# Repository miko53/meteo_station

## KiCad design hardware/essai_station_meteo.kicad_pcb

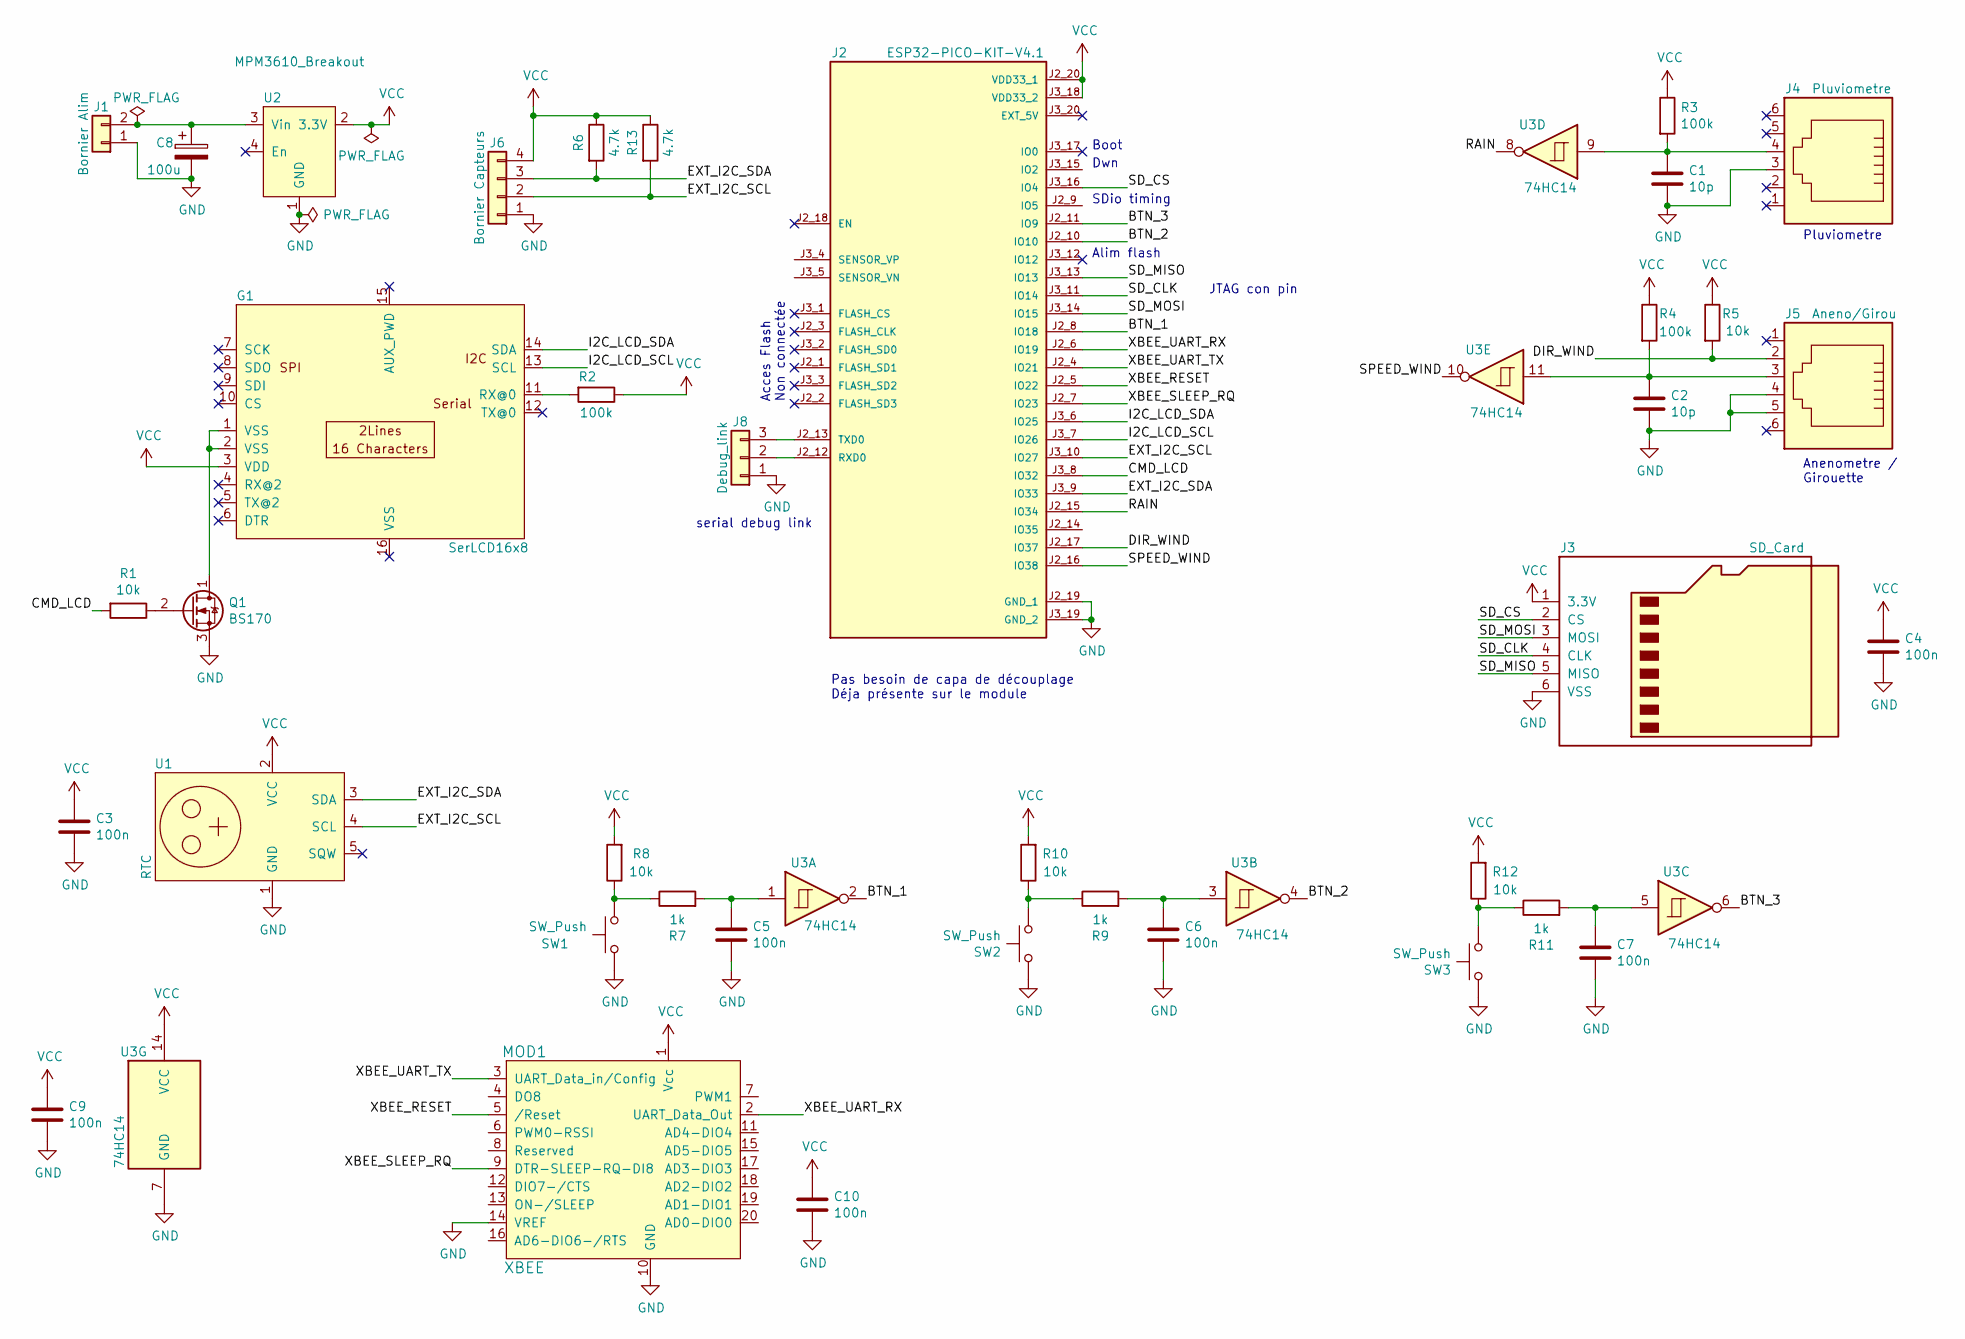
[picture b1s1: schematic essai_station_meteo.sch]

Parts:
C1, C2: 10p; C_Disc_D3.0mm_W1.6mm_P2.50mm
C3, C4, C5, C6, C7, C9, C10: 100n; C_Disc_D6.0mm_W2.5mm_P5.00mm
C8: 100u; CP_Radial_D8.0mm_P3.50mm
G1: SerLCD16x8; SerLCD16x8Sparkfun
J1: Bornier Alim; Bornier_2pts_L10mm_W7.5mm_P5mm
J2: ESP32-PICO-KIT-V4.1; XCVR_ESP32-PICO-KIT-V4.1; PARTREV 4.1
J3: SD_Card; PinHeader_1x06_P2.54mm_Vertical
J4: Pluviometre; RJ12_Amphenol_54601
J5: Aneno/Girou; RJ12_Amphenol_54601
J6: Bornier Capteurs; PinHeader_1x04_P2.54mm_Vertical
J8: Debug_link; PinHeader_1x03_P2.54mm_Vertical
MOD1: XBEE; XBEE-20_THT; MPN XB24-API-001; Digi-Key_PN 602-1273-ND
Q1: BS170; TO-92_Inline
R1, R5, R8, R10, R12: 10k; R_Axial_DIN0207_L6.3mm_D2.5mm_P10.16mm_Horizontal
R2, R3, R4: 100k; R_Axial_DIN0207_L6.3mm_D2.5mm_P10.16mm_Horizontal
R6, R13: 4.7k; R_Axial_DIN0207_L6.3mm_D2.5mm_P10.16mm_Horizontal
R7, R9, R11: 1k; R_Axial_DIN0207_L6.3mm_D2.5mm_P10.16mm_Horizontal
SW1, SW2, SW3: SW_Push; PinSocket_1x02_P2.54mm_Vertical
U1: RTC; PinHeader_1x05_P2.54mm_Vertical
U2: MPM3610_Breakout; PinSocket_1x04_P2.54mm_Vertical
U3: 74HC14; DIP-14_W7.62mm

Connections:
/BTN_1: J2.J2_8 (IO18), U3.2
/BTN_2: J2.J2_10 (IO10), U3.4
/BTN_3: J2.J2_11 (IO9), U3.6
/CMD_LCD: J2.J3_8 (IO32), R1.2
/DIR_WIND: J2.J2_17 (IO37), J5.2, R5.2
/EXT_I2C_SCL: J2.J3_10 (IO27), J6.2, R13.2, U1.4 (SCL)
/EXT_I2C_SDA: J2.J3_9 (IO33), J6.3, R6.2, U1.3 (SDA)
/I2C_LCD_SCL: G1.13 (SCL), J2.J3_7 (IO26)
/I2C_LCD_SDA: G1.14 (SDA), J2.J3_6 (IO25)
/RAIN: J2.J2_15 (IO34), U3.8
/SD_CLK: J2.J3_11 (IO14), J3.4 (CLK)
/SD_CS: J2.J3_16 (IO4), J3.2 (CS)
/SD_MISO: J2.J3_13 (IO13), J3.5 (MISO)
/SD_MOSI: J2.J3_14 (IO15), J3.3 (MOSI)
/SPEED_WIND: J2.J2_16 (IO38), U3.10
/XBEE_RESET: J2.J2_5 (IO22), MOD1.5 (/Reset); also elsewhere on the board
/XBEE_SLEEP_RQ: J2.J2_7 (IO23), MOD1.9 (DTR-SLEEP-RQ-DI8); also elsewhere on the board
/XBEE_UART_RX: J2.J2_6 (IO19), MOD1.2 (UART_Data_Out); also elsewhere on the board
/XBEE_UART_TX: J2.J2_4 (IO21), MOD1.3 (UART_Data_in/Config); also elsewhere on the board
GND: C1.2, C2.2, C3.2, C4.2, C5.2, C6.2, C7.2, C8.2, C9.2, C10.2, J1.1, J2.J2_19 (GND_1), J2.J3_19 (GND_2), J3.6 (VSS), J4.3, J5.4, J5.5, J6.1, J8.1, MOD1.10 (GND), MOD1.14 (VREF), Q1.3 (S), SW1.1, SW2.1, SW3.1, U1.1 (GND), U2.1 (GND), U3.7 (GND); also elsewhere on the board
unnamed: C1.1, J4.4, R3.2, U3.9
unnamed: C2.1, J5.3, R4.2, U3.11
unnamed: C5.1, R7.2, U3.1
unnamed: C6.1, R9.2, U3.3
unnamed: C7.1, R11.2, U3.5
unnamed: C8.1, J1.2, U2.3 (Vin)
unnamed: G1.1 (VSS), G1.2 (VSS), Q1.1 (D)
unnamed: G1.11 (RX@0), R2.2
unnamed: J2.J2_12 (RXD0), J8.2
unnamed: J2.J2_13 (TXD0), J8.3
unnamed: Q1.2 (G), R1.1
unnamed: R7.1, R8.1, SW1.2
unnamed: R9.1, R10.1, SW2.2
unnamed: R11.1, R12.1, SW3.2
VCC: C3.1, C4.1, C9.1, C10.1, G1.3 (VDD), J2.J2_20 (VDD33_1), J2.J3_18 (VDD33_2), J3.1 (3.3V), J6.4, MOD1.1 (Vcc), R2.1, R3.1, R4.1, R5.1, R6.1, R8.2, R10.2, R12.2, R13.1, U1.2 (VCC), U2.2 (3.3V), U3.14 (VCC); also elsewhere on the board

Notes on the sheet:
Pas besoin de capa de découplage Déja présente sur le module
Pluviometre
Anenometre / Girouette
serial debug link
Boot
Alim flash
Acces Flash Non connectée
Dwn
SDio timing
JTAG con pin

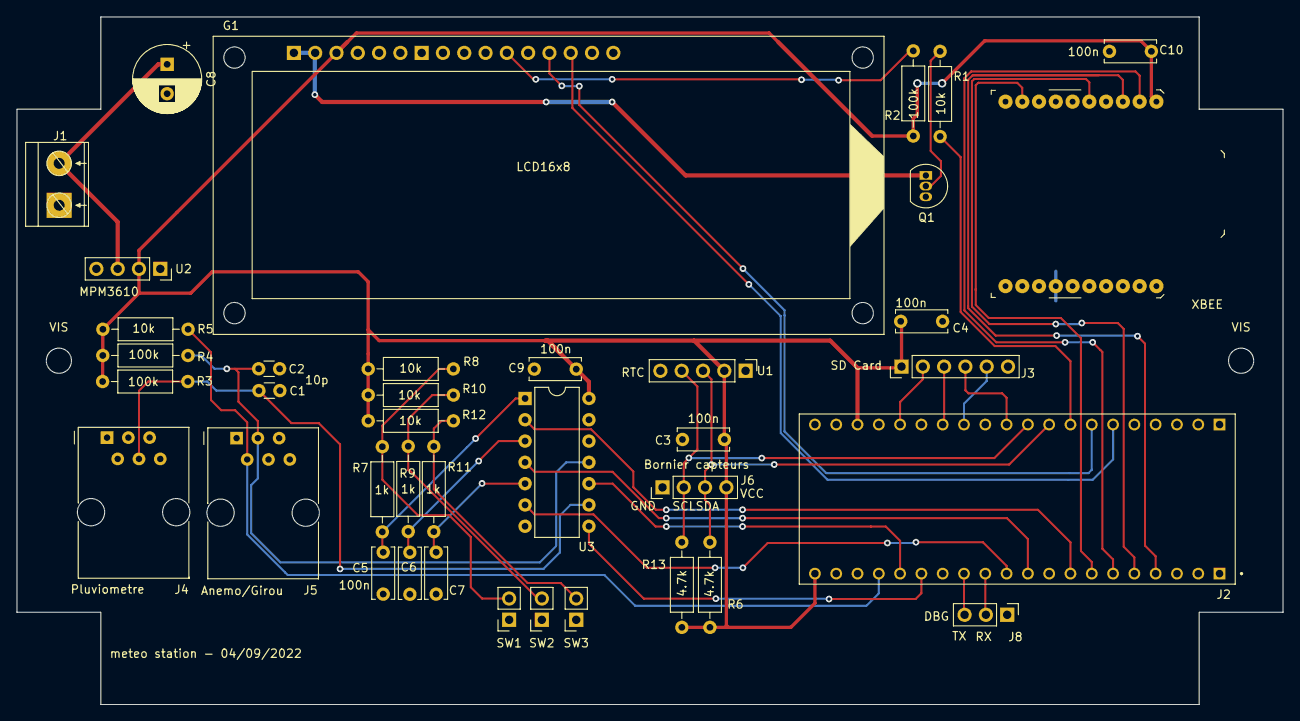
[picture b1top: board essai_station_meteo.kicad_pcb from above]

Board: 2 copper layers, 151.0 x 82.0 mm, 41 parts (0 on the bottom side), 35 nets.

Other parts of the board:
VIS: MountingHole_3mm
VIS#2: MountingHole_3mm
XBEE: XBEE; XBEE-20_THT

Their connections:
/XBEE_RESET: XBEE.5; also elsewhere on the board
/XBEE_SLEEP_RQ: XBEE.9; also elsewhere on the board
/XBEE_UART_RX: XBEE.2; also elsewhere on the board
/XBEE_UART_TX: XBEE.3; also elsewhere on the board
GND: XBEE.10, XBEE.14; also elsewhere on the board
VCC: XBEE.1; also elsewhere on the board

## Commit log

2022-09-04 schematics of meteo station
2022-09-04 add name of board + move capa to avoid RTC collision
2022-09-18 add initial readme
2022-09-24 add hello world for started...
2022-09-24 add I2C init + template of first files
2022-09-24 remove kdev file project
2022-09-25 first driver for ser_lcd screen, freely inspired from arduino one
2022-09-25 ser_lcd add new API
2022-09-25 add more API for ser_lcd, set tick to 1ms for wait time (may be review this)
2022-10-08 add first button events, work in progress
2022-10-09 add button driver
2022-10-09 add first menu, need more work (click to add in button for ex.) to save it
2022-10-10 add clicked() event
2022-10-15 clean up and reorganize menu, add setup date menu
2022-10-15 add time mgt
2022-10-15 add rtc driver for pcf8523 with date/time setting
2022-10-16 add date/time display dynamically
2022-10-16 add sdcard support
2022-10-16 add sdcard infos screen
2022-10-23 begin file log creation and fix some error on date, plus some improvement
2022-10-23 fix error when trying to send an empty line to ser_lcd
2022-10-23 create task in filelog clean up code
2022-10-29 add ctrl task + public API for filelog
2022-10-30 add modification of file when date has changed + test in ctrl task
2022-10-30 add first dev for rainmeter
2022-10-30 fix init status check
2022-10-30 add anemometer like rainmeter and modify conversion formula
2022-10-31 adapt formula according to documentation, need to be checked since the chinese version give 0.33m/s and not 0.66....
2022-10-31 add wind direction
2022-10-31 simplify including header files
2022-10-31 centralize thread info, add data_def for manage data reception in ctrl
2022-10-31 centralize configuration, remove some dbg information, add it in ctrl
2022-10-31 change log/dbg info
2022-10-31 add first log of data in sd card
2022-10-31 add API for date and write log data on SD card
2022-11-01 update gitignore for vscode
2022-11-01 first DB (trial) for doing calculation and data storage
2022-11-01 add unit test for all operation on data, first step (WIP)
2022-11-01 wip to save, first dev on data
2022-11-13 first test on cumul data
2022-11-13 add complementary test on slide part of data_operation
2022-11-20 add code for fix period and unit test for helper functions to prepare unit test
2022-11-20 add day which begins by 1
2022-11-20 add unit test
2022-11-20 add test case + bug fix for fix period feature
2022-11-21 split histogram function into a specific components
2022-11-21 add activation of data operation and rename function add in add_sample
2022-11-21 prepare new variant, fix error on default case
2022-11-22 add variant type
2022-11-22 add variant also
2022-11-22 modify add to remove dependancy to msg type
2022-11-26 renave type in sensor, clean main() function, add data acq in ctrl
2022-11-27 add config/variable for now for logging or not into sdcard
2022-11-27 fix update of PM mode on RTC
2022-11-27 add callback on new data in histo to log them
2022-12-03 adapt unit test to new API signature
2022-12-04 add histogram first menu
2022-12-04 histo test of display
2022-12-06 add histogramm screen
2022-12-10 add temporisation on screen to shutdown it when timeout expires
2022-12-10 add power shutdown of screen, ok now
2022-12-11 add storage of configuration and add filelog configuration
2022-12-24 add Bluetooth BLE first GATT server based on blehr example
2022-12-30 add ess service for BLE on wind dir wind speed and rainfall, read and notification, first implementation
2022-12-31 add time profile
2022-12-31 add ble screen configuration
2022-12-31 code little clean up on ble function
2023-01-01 remove global var, code cleaning
2023-01-01 add first zb uart interface
2023-01-02 first trial sending data by zigbee
2023-01-02 add sending sensor data on zigbee
2023-01-02 add sleep mode for zigbee
2023-02-19 fix error on ZB sending data
2023-02-19 add zb menu configuration
2023-03-05 fix error on display unit
2023-03-12 add simulated data capability
2023-03-12 fix and add compil option
2023-03-12 fix error on wrong sensor stored
2023-03-12 fix notification ble error, change some log level
2023-03-12 fix unit error
2023-03-18 minor log fix, modify frequency to decrease consumption
2023-05-18 change button order
2025-08-29 change unit for rainmeter and windspeed
